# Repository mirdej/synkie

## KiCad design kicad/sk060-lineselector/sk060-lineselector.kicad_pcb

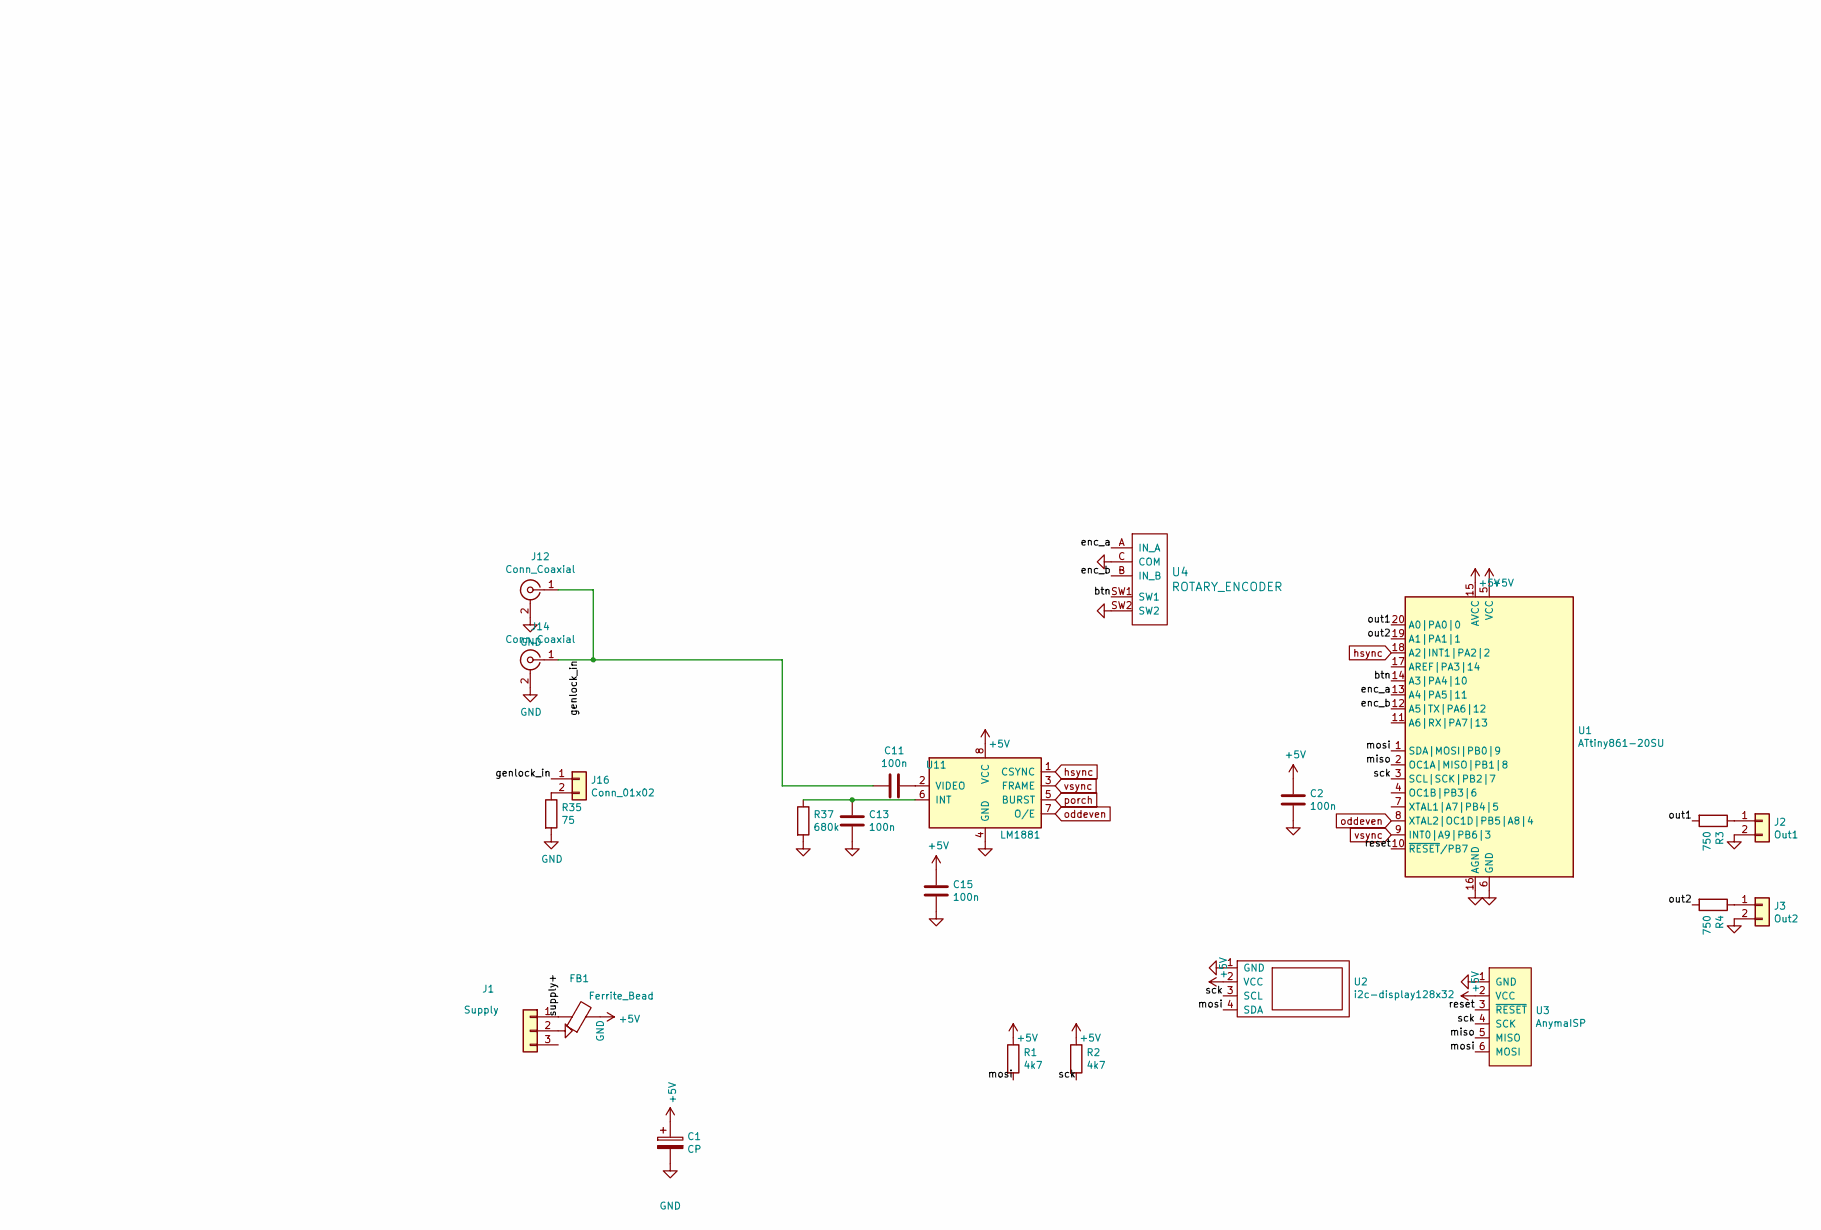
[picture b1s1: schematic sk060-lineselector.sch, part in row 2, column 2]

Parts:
C1: CP; CP_EIA-3528-21_Kemet-B_Pad1.50x2.35mm_HandSolder
C2, C11, C13, C15: 100n; C_0603_1608Metric_Pad1.05x0.95mm_HandSolder
FB1: Ferrite_Bead; L_0805_2012Metric_Pad1.15x1.40mm_HandSolder
J1: Supply; Molex_KK-254_AE-6410-03A_1x03_P2.54mm_Vertical
J2: Out1; Molex_KK-254_AE-6410-02A_1x02_P2.54mm_Vertical
J3: Out2; Molex_KK-254_AE-6410-02A_1x02_P2.54mm_Vertical
J12, J14: Conn_Coaxial; BNC_TEConnectivity_1478204_Vertical
J16: Conn_01x02; PinHeader_1x02_P2.54mm_Vertical
R1, R2: 4k7; R_0805_2012Metric_Pad1.15x1.40mm_HandSolder
R3, R4: 750; R_0805_2012Metric_Pad1.15x1.40mm_HandSolder
R35: 75; R_0805_2012Metric_Pad1.15x1.40mm_HandSolder
R37: 680k; R_0805_2012Metric_Pad1.15x1.40mm_HandSolder
U1: ATtiny861-20SU; SOIC-20W_7.5x12.8mm_P1.27mm
U2: i2c-display128x32; Bangood-OLED-128x32
U3: AnymaISP; PinHeader_1x06_P2.54mm_Vertical
U4: ROTARY_ENCODER
U11: LM1881; SOIC-8_3.9x4.9mm_P1.27mm

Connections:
+5V: C1.1, C2.1, C15.1, FB1.2, R1.1, R2.1, U1.5 (VCC), U1.15 (AVCC), U2.2 (VCC), U3.2 (VCC), U11.8 (VCC)
/btn: U1.14 (A3|PA4|10), U4.SW1
/enc_a: U1.13 (A4|PA5|11), U4.A (IN_A)
/enc_b: U1.12 (A5|TX|PA6|12), U4.B (IN_B)
/genlock_in: C11.2, J12.1 (In), J14.1 (In), J16.1
/miso: U1.2 (OC1A|MISO|PB1|8), U3.5 (MISO)
/mosi: R1.2, U1.1 (SDA|MOSI|PB0|9), U2.4 (SDA), U3.6 (MOSI)
/out1: R3.2, U1.20 (A0|PA0|0)
/out2: R4.2, U1.19 (A1|PA1|1)
/reset: U1.10 (~RESET~/PB7), U3.3 (~RESET)
/sck: R2.2, U1.3 (SCL|SCK|PB2|7), U2.3 (SCL), U3.4 (SCK)
/supply+: FB1.1, J1.1
GND: C1.2, C2.2, C13.2, C15.2, J1.2, J2.2, J3.2, J12.2 (Ext), J14.2 (Ext), R35.2, R37.2, U1.6 (GND), U1.16 (AGND), U2.1 (GND), U3.1 (GND), U4.C (COM), U4.SW2, U11.4 (GND)
unnamed: C11.1, U11.2 (VIDEO)
unnamed: C13.1, R37.1, U11.6 (INT)
unnamed: J2.1, R3.1
unnamed: J3.1, R4.1
unnamed: J16.2, R35.1
hsync: U1.18 (A2|INT1|PA2|2), U11.1 (CSYNC)
oddeven: U1.8 (XTAL2|OC1D|PB5|A8|4), U11.7 (O/E)
vsync: U1.9 (INT0|A9|PB6|3), U11.3 (FRAME)

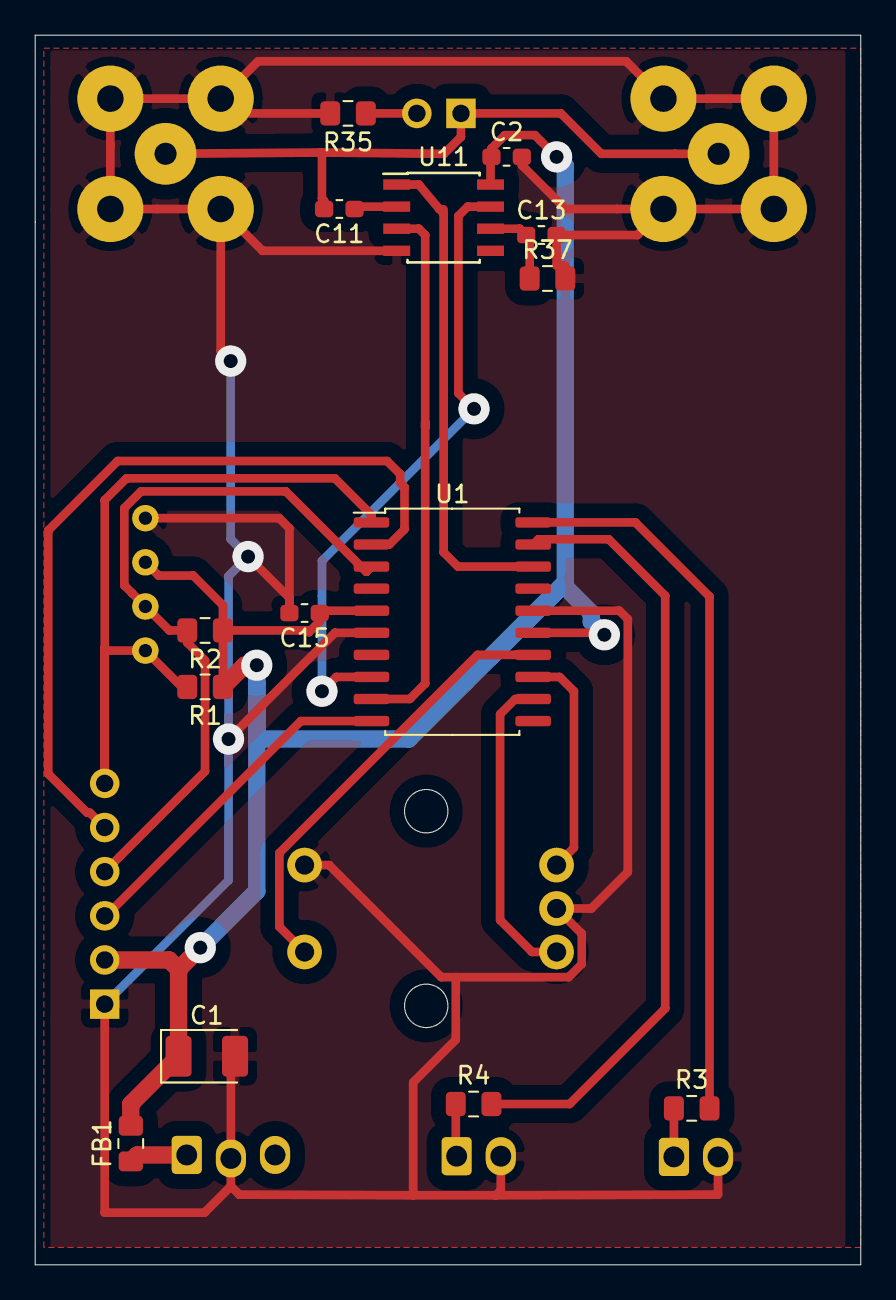
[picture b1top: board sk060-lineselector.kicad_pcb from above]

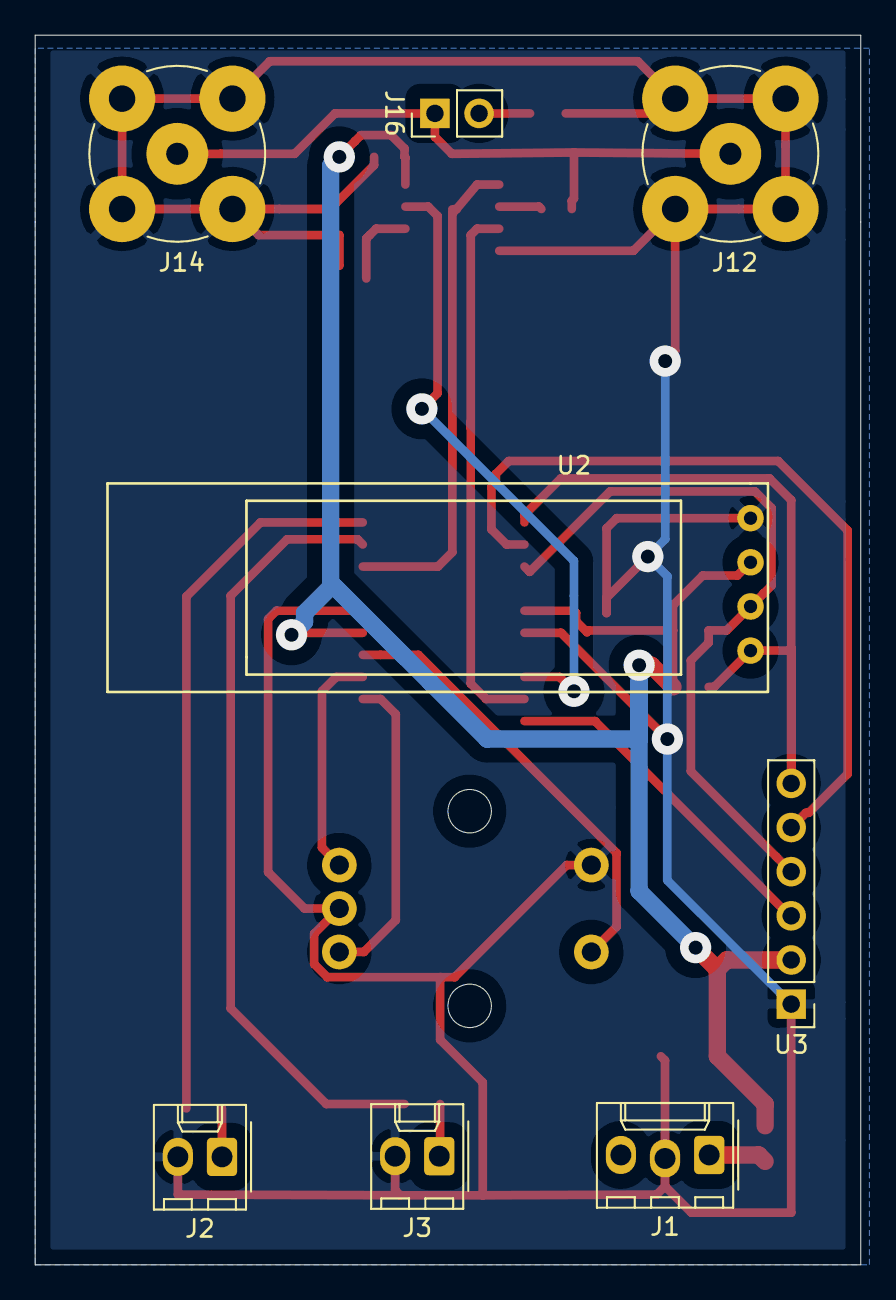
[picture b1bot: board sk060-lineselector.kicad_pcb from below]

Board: 2 copper layers, 47.5 x 70.8 mm, 23 parts (9 on the bottom side), 21 nets.

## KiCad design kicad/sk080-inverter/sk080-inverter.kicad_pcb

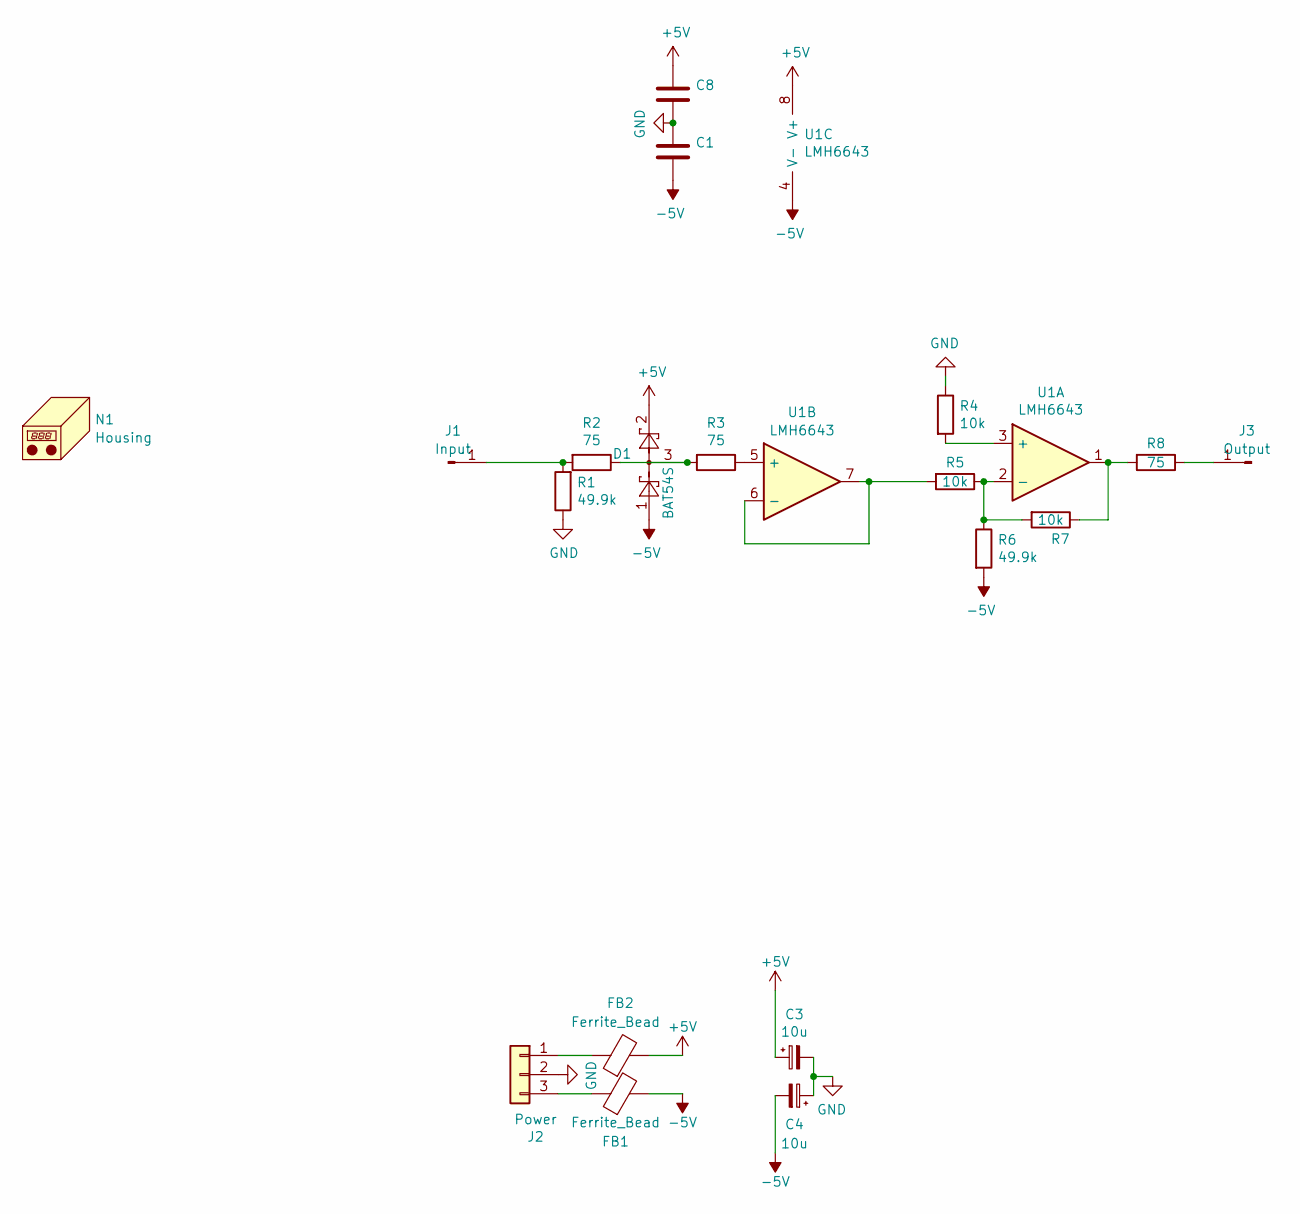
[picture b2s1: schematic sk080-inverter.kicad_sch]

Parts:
C1, C8: 100n; C_0603_1608Metric; LCSC C14663
C3, C4: 10u; C_0805_2012Metric; LCSC C15850
D1: BAT54S; SOT-23; LCSC C8592
FB1, FB2: Ferrite_Bead; L_0805_2012Metric; LCSC C1017
J1: Input; Banana2mm-Löthülse
J2: Power; Molex_KK-254_AE-6410-03A_1x03_P2.54mm_Vertical_SMD
J3: Output; Banana2mm-Löthülse
N1: Housing; Frontplate_10mm
R1, R6: 49.9k; R_0603_1608Metric; LCSC C23184
R2, R3, R8: 75; R_0603_1608Metric; LCSC C4275
R4, R5, R7: 10k; R_0603_1608Metric; LCSC C25804
U1: LMH6643; VSSOP-8_3x3mm_P0.65mm; LCSC C478382

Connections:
+5V: C3.1, C8.1, D1.2, FB2.2, U1.8 (V+)
-5V: C1.2, C4.2, D1.1, FB1.2, R6.2, U1.4 (V-)
GND: C1.1, C3.2, C4.1, C8.2, J2.2, R1.1, R4.1
unnamed: D1.3, R2.1, R3.2
unnamed: J1.1, R1.2, R2.2
unnamed: FB2.1, J2.1
unnamed: FB1.1, J2.3
unnamed: J3.1, R8.1
unnamed: R7.1, R8.2, U1.1
unnamed: R4.2, U1.3 (+)
unnamed: R5.1, R6.1, R7.2, U1.2 (-)
unnamed: R3.1, U1.5 (+)
unnamed: R5.2, U1.6 (-), U1.7

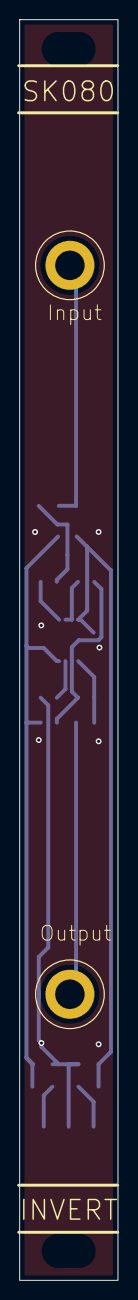
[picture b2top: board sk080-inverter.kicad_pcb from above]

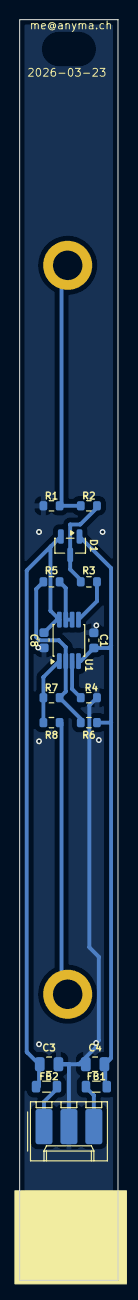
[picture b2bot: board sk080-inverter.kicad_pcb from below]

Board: 2 copper layers, 10.0 x 128.5 mm, 20 parts (17 on the bottom side), 13 nets.

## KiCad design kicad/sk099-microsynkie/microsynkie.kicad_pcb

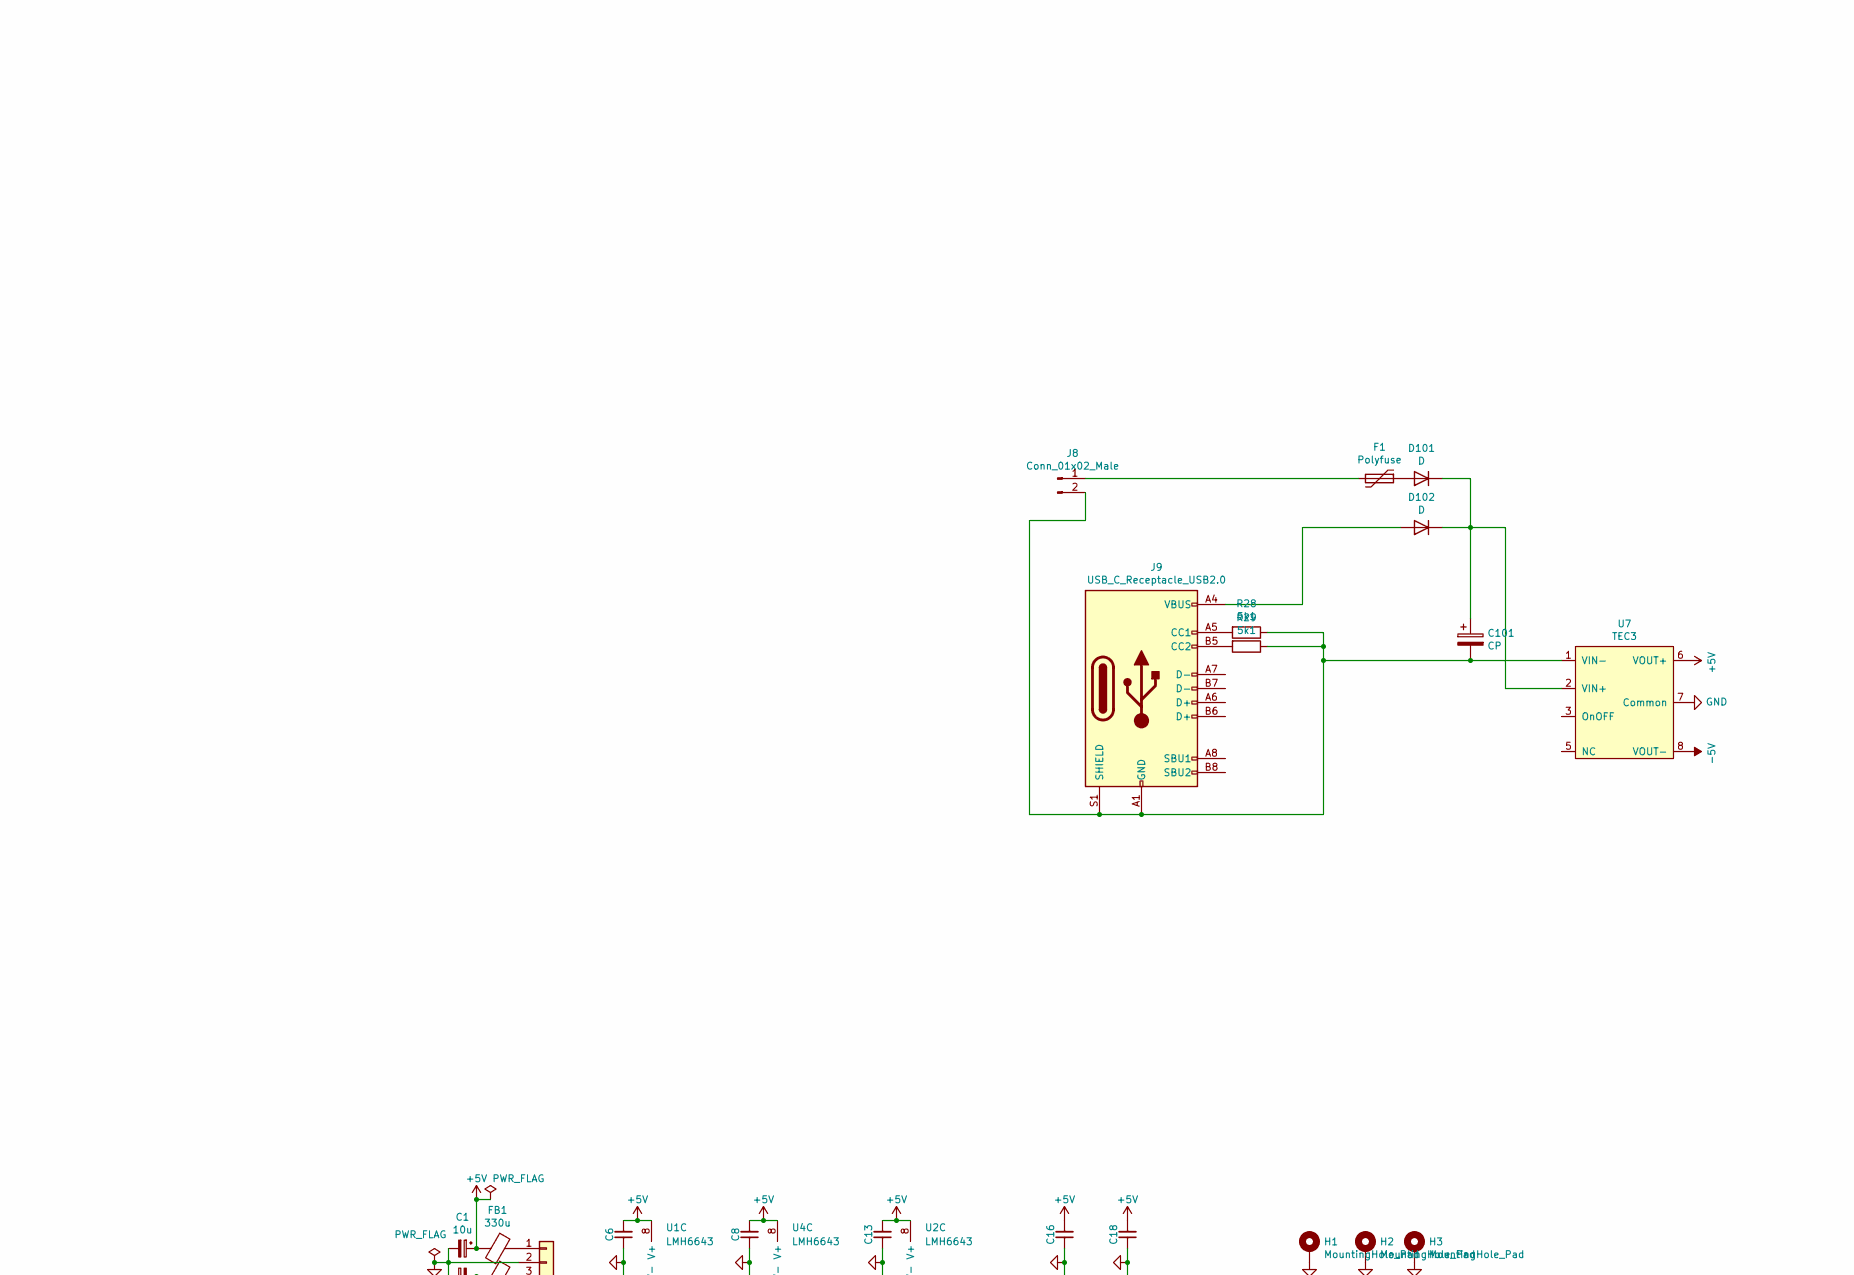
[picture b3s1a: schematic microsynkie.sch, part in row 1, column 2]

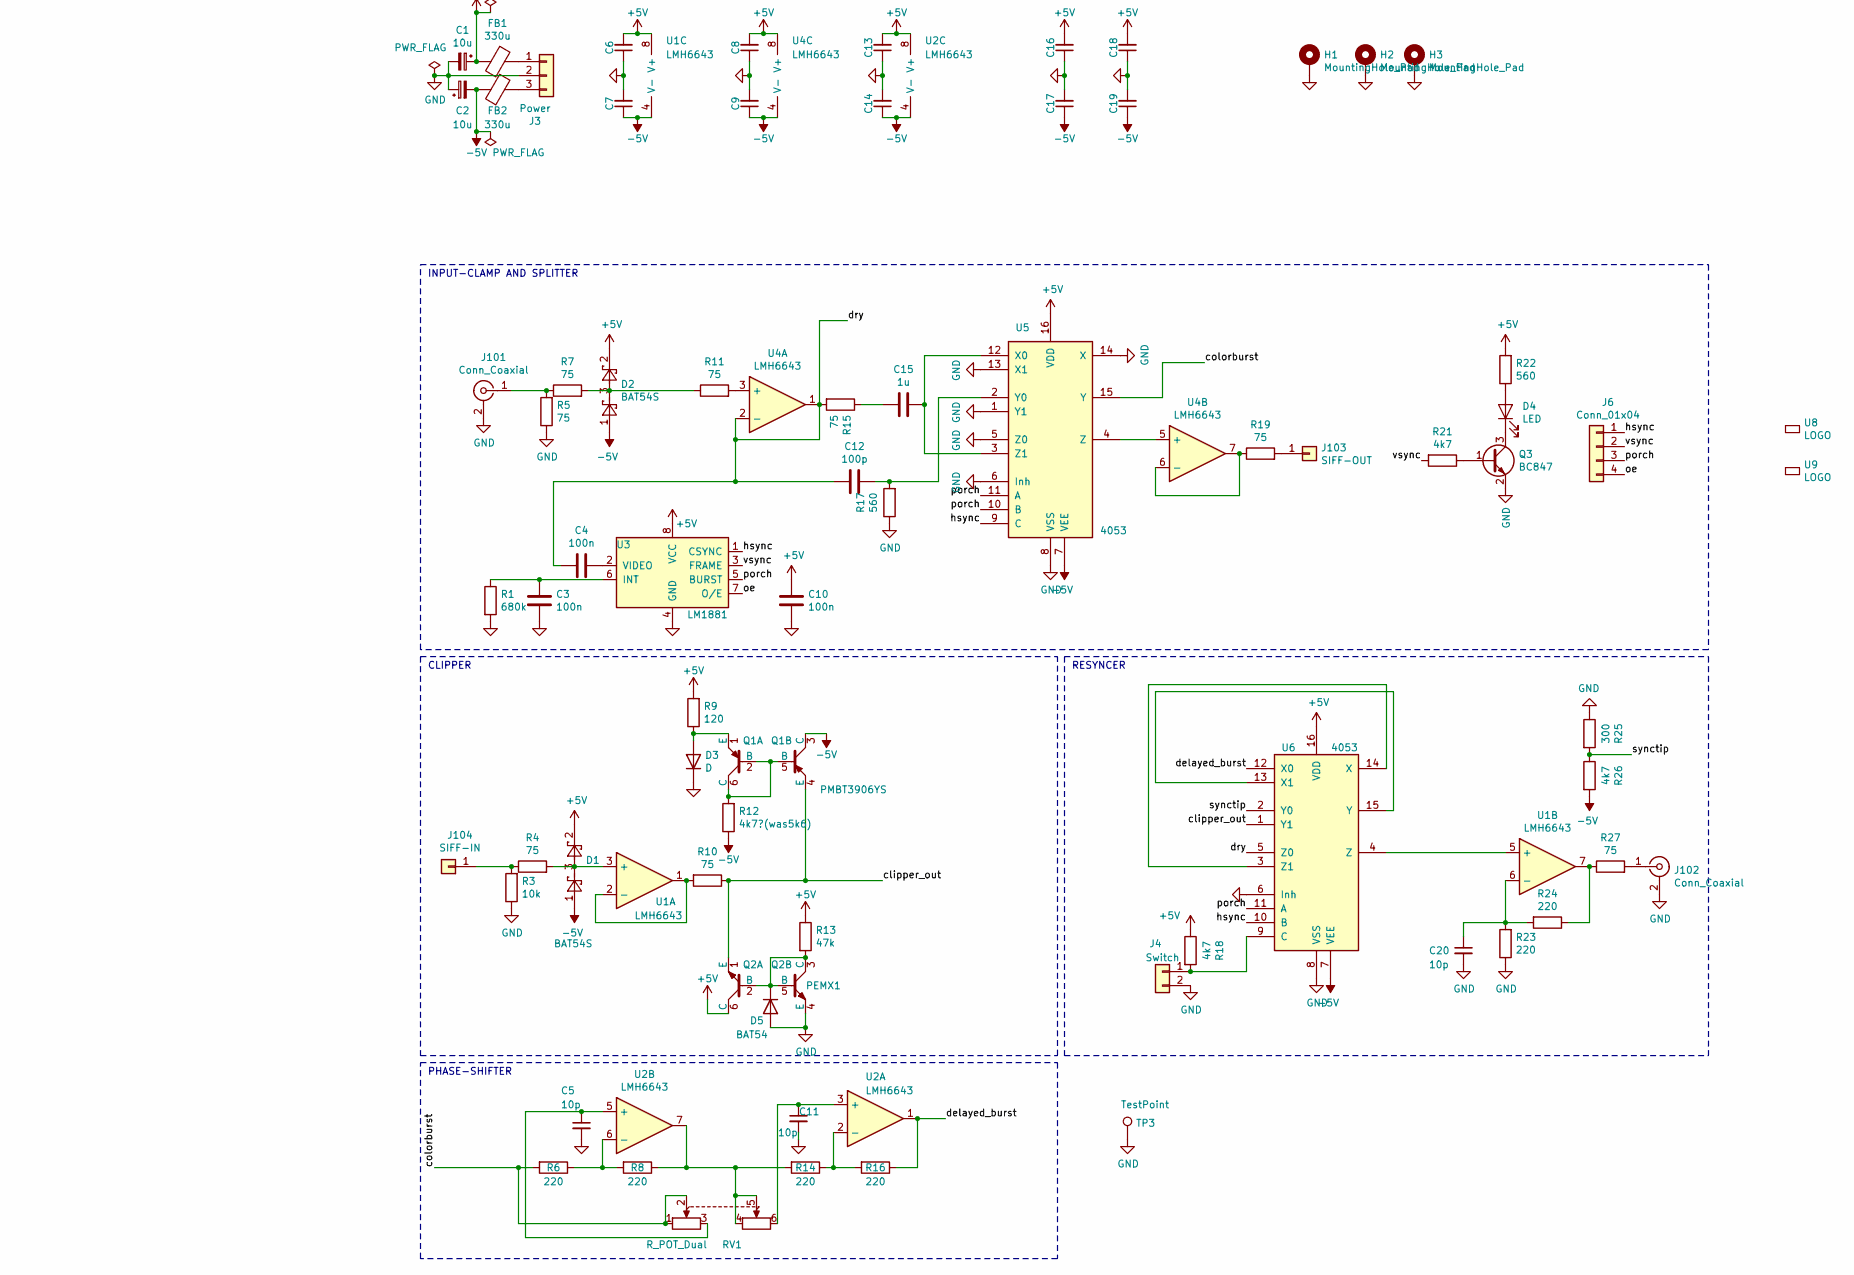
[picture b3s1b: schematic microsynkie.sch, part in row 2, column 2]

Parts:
C1, C2: 10u; CP_EIA-3528-21_Kemet-B_Pad1.50x2.35mm_HandSolder
C3, C4, C6, C7, C8, C9, C10, C13, C14, C16, C17, C18, C19: 100n; C_0603_1608Metric_Pad1.05x0.95mm_HandSolder
C5, C11, C20: 10p; C_0805_2012Metric_Pad1.15x1.40mm_HandSolder
C12: 100p; C_1206_3216Metric_Pad1.42x1.75mm_HandSolder
C15: 1u; C_0603_1608Metric_Pad1.05x0.95mm_HandSolder
C101: CP; CP_Elec_10x10.5
D1, D2: BAT54S; SOT-23
D3, D101, D102: D; D_MiniMELF
D4: LED; LED_D3.0mm
D5: BAT54; D_SOT-23_ANK
F1: Polyfuse; C_0805_2012Metric_Pad1.15x1.40mm_HandSolder
FB1, FB2: 330u; L_1206_3216Metric_Pad1.42x1.75mm_HandSolder
H1, H2, H3: MountingHole_Pad; MountingHole_2.7mm_M2.5_ISO7380_Pad
J3: Power; Molex_KK-254_AE-6410-03A_1x03_P2.54mm_Vertical
J4: Switch; PinHeader_1x02_P2.54mm_Vertical
J6: Conn_01x04; Molex_KK-254_AE-6410-04A_1x04_P2.54mm_Vertical
J8: Conn_01x02_Male; Molex_KK-254_AE-6410-02A_1x02_P2.54mm_Vertical
J9: USB_C_Receptacle_USB2.0; JAE_USB-C_SJ122205
J101, J102: Conn_Coaxial; BNC_MOLEX_0731000080_Horizontal
J103: SIFF-OUT; Solderpad_1mm
J104: SIFF-IN; Solderpad_1mm
Q1: PMBT3906YS; SOT-363_SC-70-6_Handsoldering
Q2: PEMX1; SOT-666
Q3: BC847; SOT-23
R1: 680k; R_0805_2012Metric_Pad1.15x1.40mm_HandSolder
R3: 10k; R_0805_2012Metric_Pad1.15x1.40mm_HandSolder
R4, R5, R7, R10, R11, R15, R19, R27: 75; R_0805_2012Metric_Pad1.15x1.40mm_HandSolder
R6, R8, R14, R16, R23, R24: 220; R_0805_2012Metric_Pad1.15x1.40mm_HandSolder
R9: 120; R_0805_2012Metric_Pad1.15x1.40mm_HandSolder
R12: 4k7?(was5k6); R_0805_2012Metric_Pad1.15x1.40mm_HandSolder
R13: 47k; R_0805_2012Metric_Pad1.15x1.40mm_HandSolder
R17, R22: 560; R_0805_2012Metric_Pad1.15x1.40mm_HandSolder
R18, R21, R26: 4k7; R_0805_2012Metric_Pad1.15x1.40mm_HandSolder
R25: 300; R_0805_2012Metric_Pad1.15x1.40mm_HandSolder
R28, R29: 5k1; R_0805_2012Metric_Pad1.15x1.40mm_HandSolder
RV1: R_POT_Dual; RK12L123
TP3: TestPoint; Solderpad_1mm
U1, U2, U4: LMH6643; SOIC-8_3.9x4.9mm_P1.27mm
U3: LM1881; SOIC-8_3.9x4.9mm_P1.27mm
U5, U6: 4053; SOIC-16_3.9x9.9mm_P1.27mm
U7: TEC3; TEC
U8: LOGO; logo_anyma_tiny
U9: LOGO; OSHW-Logo2_7.3x6mm_SilkScreen

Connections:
+5V: C1.1, C6.2, C8.2, C10.1, C13.2, C16.2, C18.2, D1.2, D2.2, FB1.2, Q2.6 (C), R9.2, R13.1, R18.1, R22.2, U1.8 (V+), U2.8 (V+), U3.8 (VCC), U4.8 (V+), U5.16 (VDD), U6.16 (VDD), U7.6 (VOUT+)
-5V: C2.2, C7.1, C9.1, C14.1, C17.1, C19.1, D1.1, D2.1, FB2.2, Q1.3 (C), R12.1, R26.2, U1.4 (V-), U2.4 (V-), U4.4 (V-), U5.7 (VEE), U6.7 (VEE), U7.8 (VOUT-)
/clipper_out: Q1.4 (E), Q2.1 (E), R10.1, U6.1 (Y1)
/colorburst: R6.2, RV1.1, RV1.2, U5.15 (Y)
/delayed_burst: R16.1, U2.1, U6.12 (X0)
/dry: C4.2, C12.2, R15.2, U4.1, U4.2 (-), U6.5 (Z0)
/hsync: J6.1, U3.1 (CSYNC), U5.9 (C), U6.10 (B)
/oe: J6.4, U3.7 (O/E)
/porch: J6.3, U3.5 (BURST), U5.10 (B), U5.11 (A), U6.11 (A)
/synctip: R25.2, R26.1, U6.2 (Y0)
/vsync: J6.2, R21.2, U3.3 (FRAME)
GND: C1.2, C2.1, C3.2, C5.2, C6.1, C7.2, C8.1, C9.2, C10.2, C11.2, C13.1, C14.2, C16.1, C17.2, C18.1, C19.2, C20.2, D3.1 (K), D5.2 (A), H1.1, H2.1, H3.1, J3.2, J4.2, J101.2 (Ext), J102.2 (Ext), Q2.4 (E), Q3.2 (E), R1.2, R3.1, R5.1, R17.1, R23.1, R25.1, TP3.1, U3.4 (GND), U5.1 (Y1), U5.5 (Z0), U5.6 (Inh), U5.8 (VSS), U5.13 (X1), U5.14 (X), U6.6 (Inh), U6.8 (VSS), U7.7 (Common)
unnamed: C3.1, R1.1, U3.6 (INT)
unnamed: C4.1, U3.2 (VIDEO)
unnamed: C5.1, RV1.3, U2.5 (+)
unnamed: C11.1, RV1.6, U2.3 (+)
unnamed: C12.1, R17.2, U5.2 (Y0)
unnamed: C15.1, U5.3 (Z1), U5.12 (X0)
unnamed: C15.2, R15.1
unnamed: C20.1, R23.2, R24.2, U1.6 (-)
unnamed: C101.1, D101.1 (K), D102.1 (K), U7.2 (VIN+)
unnamed: C101.2, J8.2, J9.A1 (GND), J9.A12 (GND), J9.B1 (GND), J9.B12 (GND), J9.S1 (SHIELD), R28.1, R29.1, U7.1 (VIN-)
unnamed: D1.3, R4.2, U1.3 (+)
unnamed: D2.3, R7.2, R11.1
unnamed: D3.2 (A), Q1.1 (E), R9.1
unnamed: D4.1 (K), Q3.3 (C)
unnamed: D4.2 (A), R22.1
unnamed: D5.1 (K), Q2.2 (B), Q2.3 (C), Q2.5 (B), R13.2
unnamed: D101.2 (A), F1.1
unnamed: D102.2 (A), J9.A4 (VBUS), J9.A9 (VBUS), J9.B4 (VBUS), J9.B9 (VBUS)
unnamed: F1.2, J8.1
unnamed: FB1.1, J3.1
unnamed: FB2.1, J3.3
unnamed: J4.1, R18.2, U6.9 (C)
unnamed: J9.A5 (CC1), R28.2
unnamed: J9.B5 (CC2), R29.2
unnamed: J101.1 (In), R5.2, R7.1
unnamed: J102.1 (In), R27.2
unnamed: J103.1, R19.2
unnamed: J104.1, R3.2, R4.1
unnamed: Q1.2 (B), Q1.5 (B), Q1.6 (C), R12.2
unnamed: Q3.1 (B), R21.1
unnamed: R6.1, R8.2, U2.6 (-)
unnamed: R10.2, U1.1, U1.2 (-)
unnamed: R11.2, U4.3 (+)
unnamed: R14.1, R16.2, U2.2 (-)
unnamed: R8.1, R14.2, RV1.4, RV1.5, U2.7
unnamed: R19.1, U4.6 (-), U4.7
unnamed: R24.1, R27.1, U1.7
unnamed: U1.5 (+), U6.4 (Z)
unnamed: U4.5 (+), U5.4 (Z)
unnamed: U6.13 (X1), U6.15 (Y)
unnamed: U6.3 (Z1), U6.14 (X)

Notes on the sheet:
PHASE-SHIFTER
CLIPPER
RESYNCER
INPUT-CLAMP AND SPLITTER

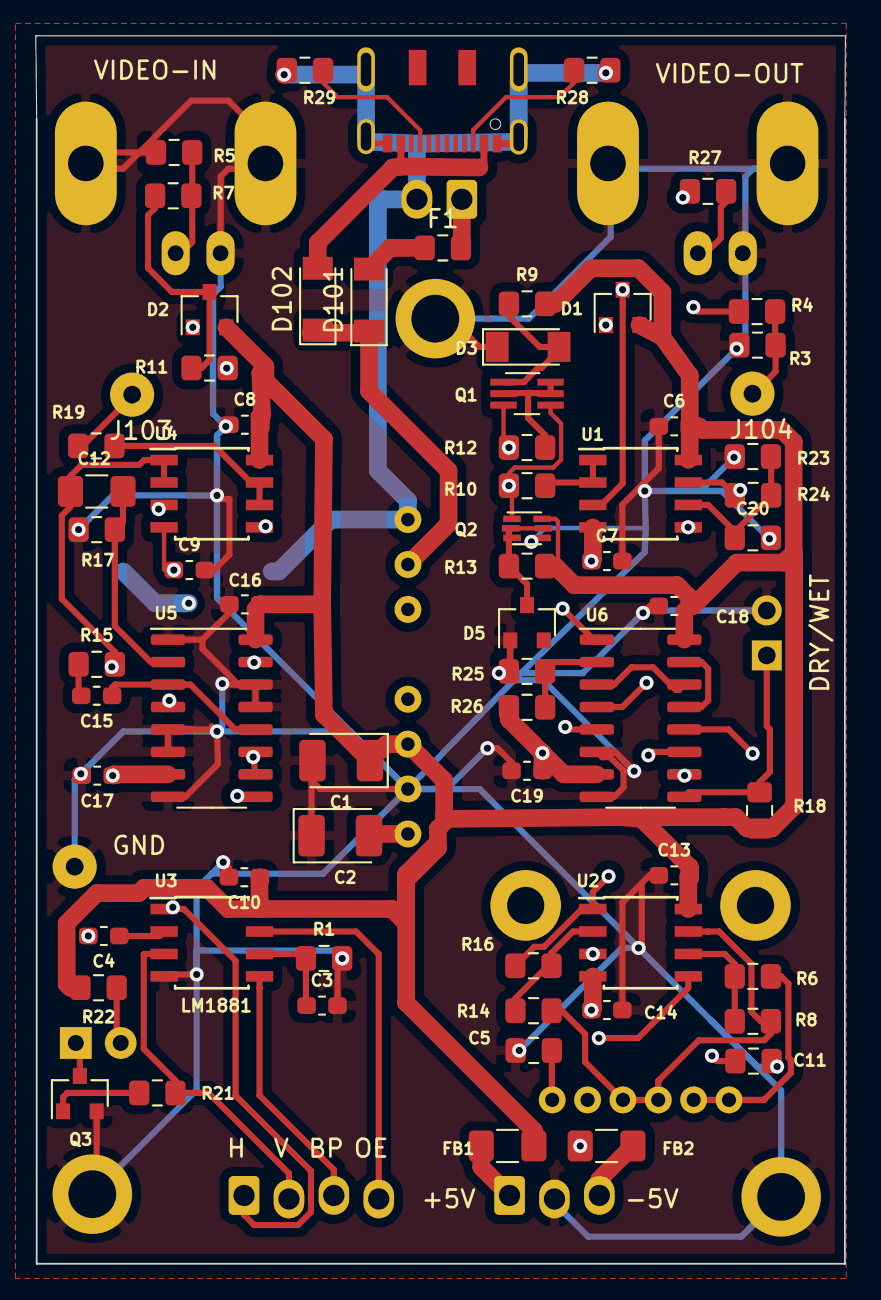
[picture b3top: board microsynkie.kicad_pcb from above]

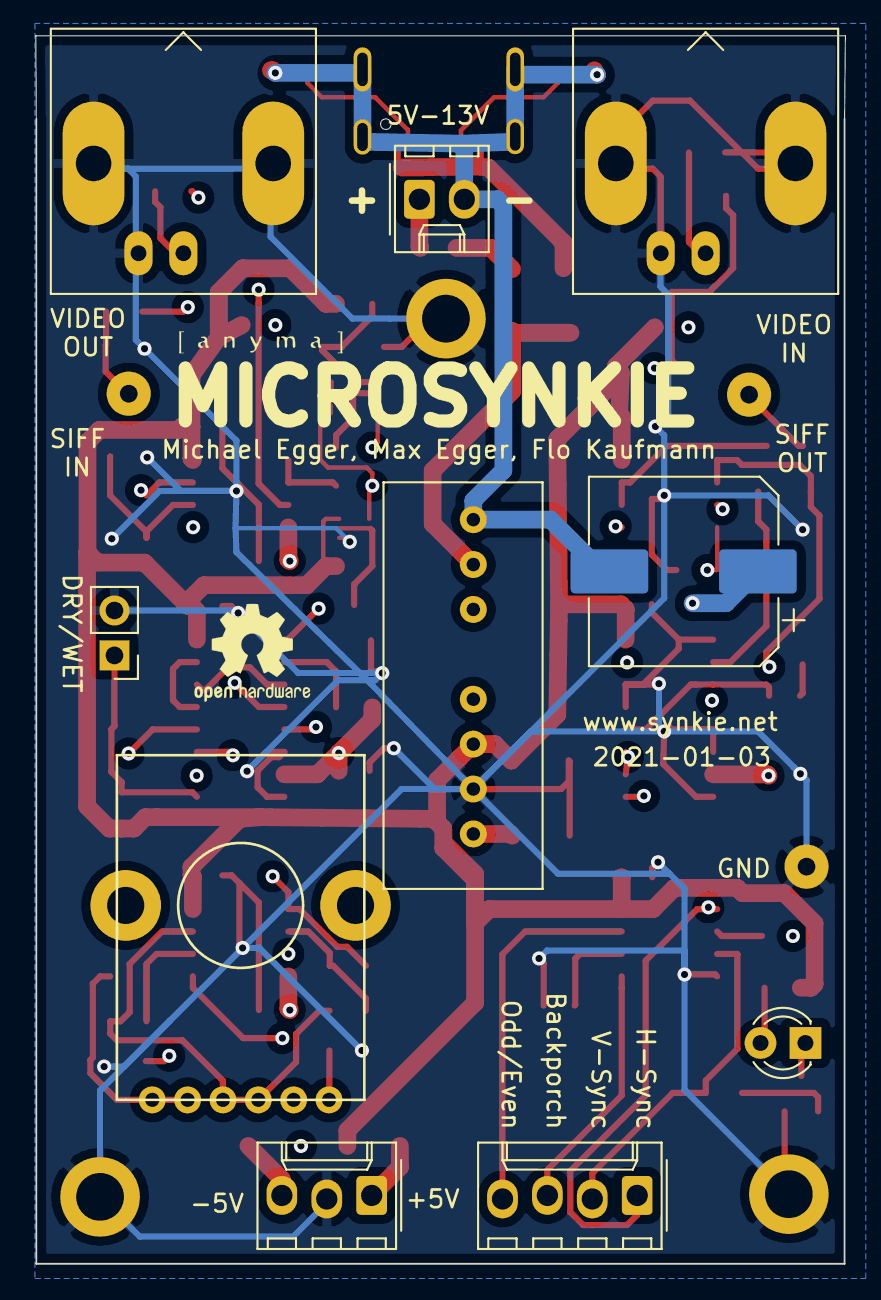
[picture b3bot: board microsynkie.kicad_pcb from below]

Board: 4 copper layers, 45.8 x 69.5 mm, 83 parts (11 on the bottom side), 53 nets.

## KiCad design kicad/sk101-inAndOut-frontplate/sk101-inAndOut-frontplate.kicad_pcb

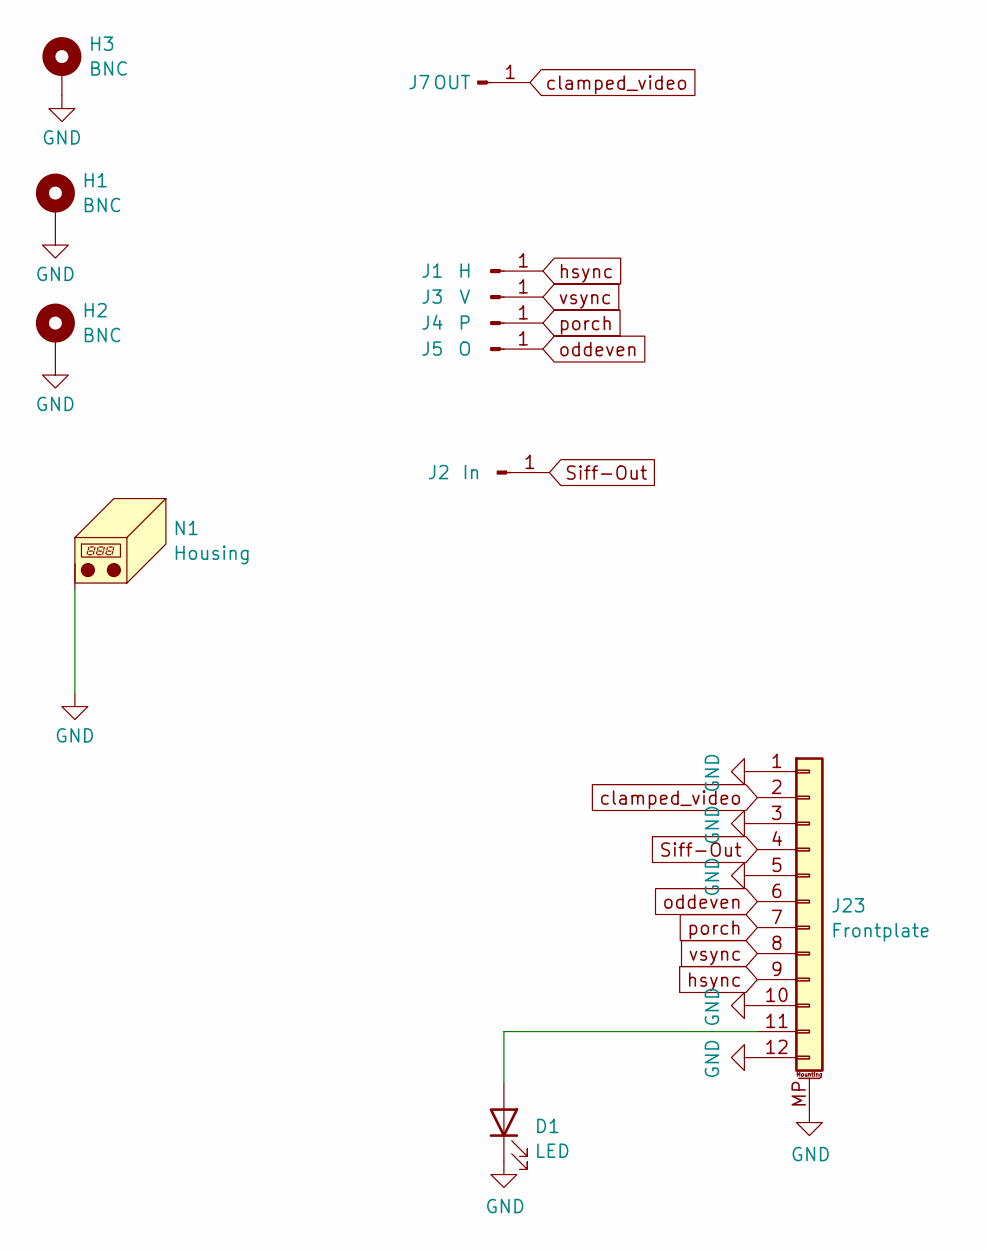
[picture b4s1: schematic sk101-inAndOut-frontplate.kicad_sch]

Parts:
D1: LED; LED_1206_3216Metric_ReverseMount_Hole1.8x2.4mm; LCSC C125108
H1, H2, H3: BNC; BNC_Ali_Frontplate
J1: H; Banana2mm-Löthülse
J2: In; Banana2mm-Löthülse
J3: V; Banana2mm-Löthülse
J4: P; Banana2mm-Löthülse
J5: O; Banana2mm-Löthülse
J7: OUT; Banana2mm-Löthülse
J23: Frontplate; AFC04-S12FCC-00; LCSC C21275
N1: Housing; Frontplate_20mm

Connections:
GND: D1.1 (K), H1.1 (1_1), H2.1 (1_1), H3.1 (1_1), J23.1, J23.3, J23.5, J23.10, J23.12, J23.MP (MountPin), N1.1 (PAD_1)
unnamed: D1.2 (A), J23.11
Siff-Out: J2.1 (Pin_1_1), J23.4
clamped_video: J7.1 (Pin_1_1), J23.2
hsync: J1.1 (Pin_1_1), J23.9
oddeven: J5.1 (Pin_1_1), J23.6
porch: J4.1 (Pin_1_1), J23.7
vsync: J3.1 (Pin_1_1), J23.8

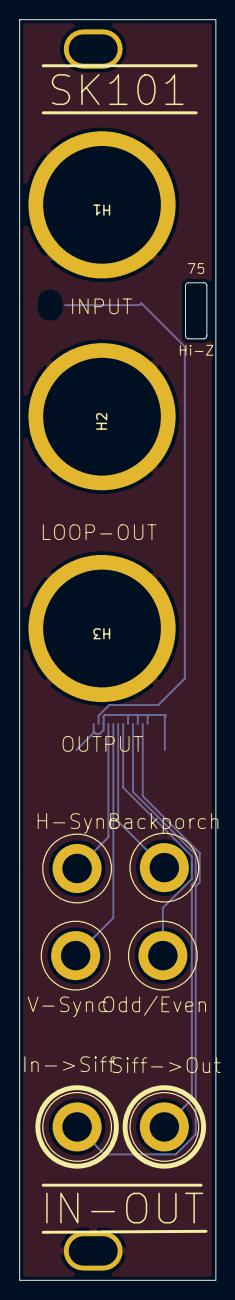
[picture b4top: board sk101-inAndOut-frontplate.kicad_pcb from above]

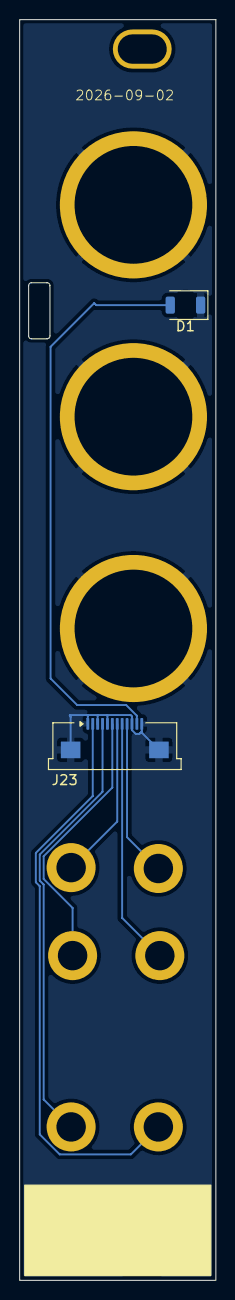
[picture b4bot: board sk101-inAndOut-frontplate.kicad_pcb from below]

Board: 2 copper layers, 20.0 x 128.5 mm, 12 parts (2 on the bottom side), 8 nets.
